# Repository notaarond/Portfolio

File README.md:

# My Small Work Collection !

Some PCB Projects I've done:

- Breakout Board for a TPS3702 Voltage Watchdog Chip
- The "Powerboard":  A Power Hub PCB with 3 Voltage Regulators and Headers for Each
- Sprinkle: ESP-32 based Avionics Board for a 2-Stage Rocket (currently still in progress)
  - not my original design, but was handed over to me minimize and add new sensors, test points, storage systems, and to do some general cleaning up of schematics and silkscreen!

Projects done in Altium or Kicad 7 :)

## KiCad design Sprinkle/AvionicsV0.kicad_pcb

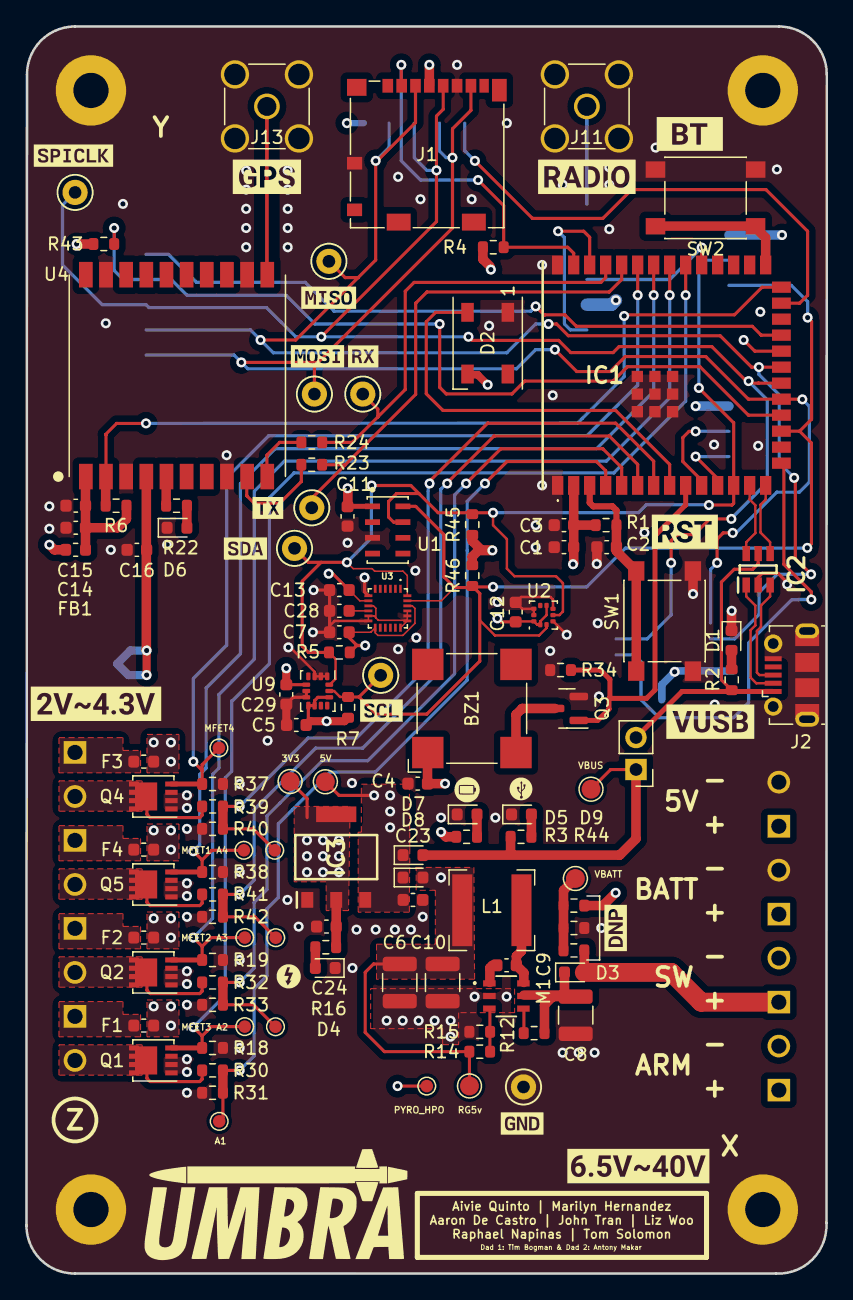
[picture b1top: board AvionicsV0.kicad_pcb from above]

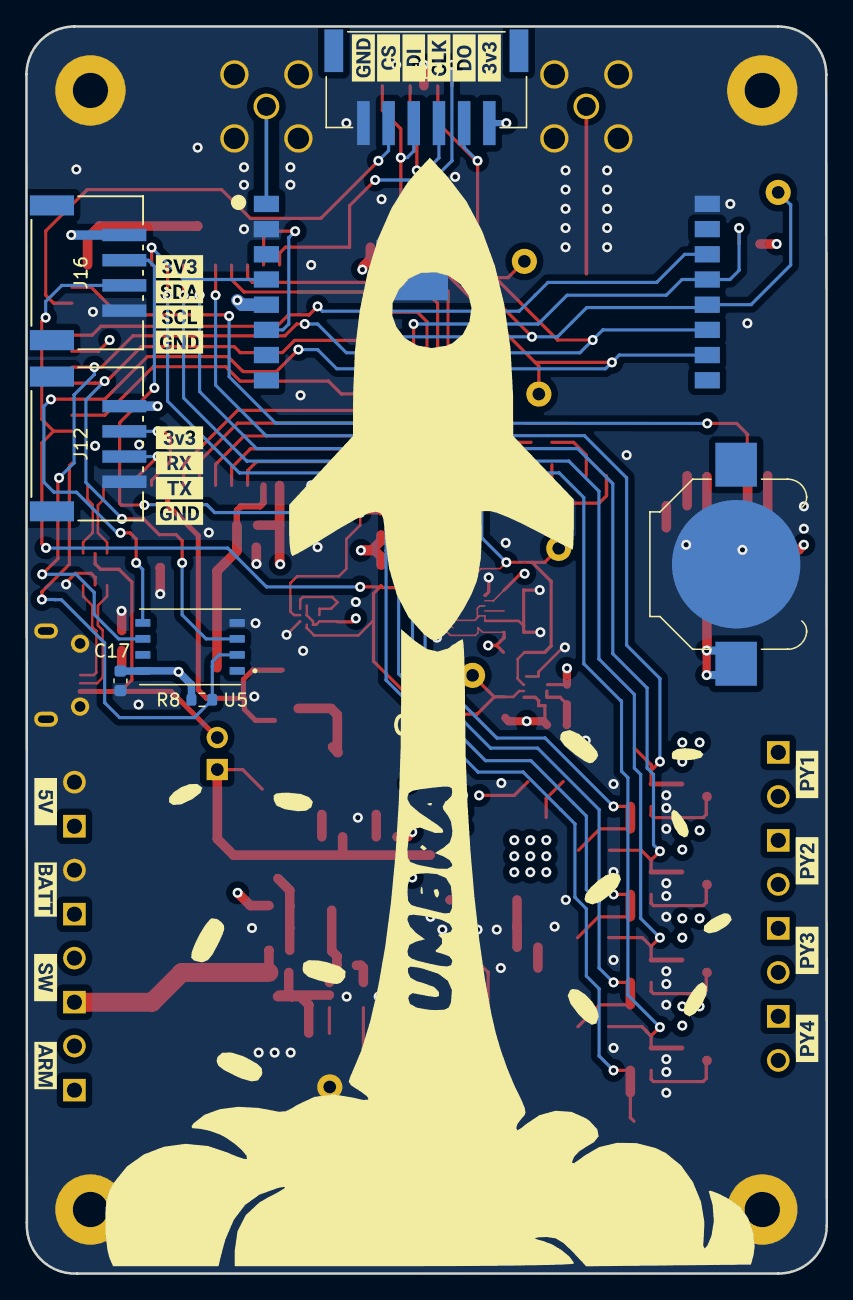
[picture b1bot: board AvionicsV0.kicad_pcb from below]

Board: 4 copper layers, 63.5 x 99.0 mm, 171 parts (30 on the bottom side), 68 nets.

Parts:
BT1: 3.7V LION; BatteryHolder_Keystone_3000_1x12mm
BZ1: Buzzer; MagneticBuzzer_CUI_CMT-8504-100-SMT
C1: 22uF; C_0603_1608Metric
C2, C14, C16: 1uF; C_0603_1608Metric
C3, C12: 100nF; C_0603_1608Metric
C4, C23, C24: 10uF; C_0603_1608Metric
C5, C29: 100 nF; C_0603_1608Metric
C6, C10: 22u; C_1210_3225Metric
C7, C13, C28: 0.1 uF; C_0603_1608Metric
C8: 47u; C_1210_3225Metric
C9: 100n; C_0603_1608Metric
C11: 220nF; C_0603_1608Metric
C15: 0.01uF; C_0603_1608Metric
C17: 0.1uF; C_0603_1608Metric
D1, D4, D5, D6, D9: LED; LED_0603_1608Metric
D2: NeoPixel_THT; LED_WS2812B_PLCC4_5.0x5.0mm_P3.2mm
D3, D7, D8: D_Schottky; D_0603_1608Metric
F1, F2, F3, F4: Fuse; Fuse_0603_1608Metric
FB1: FerriteBead; L_0603_1608Metric
H1, H2, H3, H4: MountingHole_Pad; MountingHole_3.5mm_Pad
IC1: ESP32-S3-WROOM-1U-N4R2; ESP32S3WROOM1UN4R2
IC2: USBLC6-2SC6; SOT95P280X145-6N
IC3: NCP1117IST33T3G; SOT230P700X180-4N
J1: Micro_SD_Card; microSD_HC_Molex_104031-0811
J2: USB_B_Micro; USB_Micro-B_Molex-105017-0001
J3, J4, J6, J7, J8, J9, J10, J14: Conn_01x02; OST_OSTTE020104
J5: Conn_01x02; PinHeader_1x02_P2.54mm_Vertical
J11, J13: Conn_Coaxial; SMA_Amphenol_901-144_Vertical
J12, J16: Conn_01x04; CONN_S4B-PH-SM4-TBLFSN_JST
J17: Conn_01x06; JST_S6B-PH-SM4-TB(LF)(SN)
L1: 22u; L_Bourns-SRN6028
M1: TP6841S6-A; SOT32-6 TP6841S6-TP6841S6-A
Q1, Q2, Q4, Q5: SIR182DP-T1-RE3; Vishay_PowerPAK_1212-8_Single
Q3: 2N7002H; SOT-23
R1, R4, R6, R8, R34, R43: 10k; R_0603_1608Metric
R2, R3, R44: 100; R_0603_1608Metric
R5, R7, R45, R46: 4.7k; R_0603_1608Metric
R10, R30, R32, R39, R41: 350k; R_0603_1608Metric
R11, R12, R31, R33, R40, R42: 100k; R_0603_1608Metric
R13: 0; R_0603_1608Metric
R14: 126k; R_0603_1608Metric
R15: 24k; R_0603_1608Metric
R16: 65; R_0603_1608Metric
R18, R19, R37, R38: 1k; R_0603_1608Metric
R22, R23, R24: 470; R_0603_1608Metric
SW1, SW2: SW_Push; SW_Push_1P1T_NO_6x6mm_H9.5mm
TP1: Vbatt TP; TestPoint_Pad_D1.5mm
TP2: GND TP; TestPoint_Keystone_5000-5004_Miniature
TP3: 3V3 TP; TestPoint_Pad_D1.5mm
TP4: 5V TP; TestPoint_Pad_D1.5mm
TP5: Vbus TP; TestPoint_Pad_D1.5mm
TP6: RG5 TP; TestPoint_Pad_D1.5mm
TP7: SCL TP; TestPoint_Keystone_5000-5004_Miniature
TP8: SDA TP; TestPoint_Keystone_5000-5004_Miniature
TP9: GPS-TX-UART TP; TestPoint_Keystone_5000-5004_Miniature
TP10: GPS-RX-UART-TP; TestPoint_Keystone_5000-5004_Miniature
TP13: SPI-MISO; TestPoint_Keystone_5000-5004_Miniature
TP14: SPI-MOSI; TestPoint_Keystone_5000-5004_Miniature
TP15: SPI-CLK; TestPoint_Keystone_5000-5004_Miniature
TP16: Pyro-MFET4-TP; TestPoint_Pad_D1.0mm
TP17: Pyro-MFET1-TP; TestPoint_Pad_D1.0mm
TP18, TP19: Pyro-MFET2-TP; TestPoint_Pad_D1.0mm
TP20: Pyro-HPO-TP; TestPoint_Pad_D1.0mm
TP21: Cont-A4-TP; TestPoint_Pad_D1.0mm
TP22: Cont-A3-TP; TestPoint_Pad_D1.0mm
TP23: Cont-A2-TP; TestPoint_Pad_D1.0mm
TP24: Cont-A1-TP; TestPoint_Pad_D1.0mm
U1: MS8607; MS860702BA01-50
U2: LPS22HB; ST_HLGA-10_2x2mm_P0.5mm_LayoutBorder3x2y
U3: ICM-20649; QFN40P300X300X95-24N
U4: FGPMMOPA6H
U5: XTSD04GLGEAG; SON127P600X800X95-8N
U8: RFM98PW; RFM95PW
U9: LSM6DS3; LGA-14_3x2.5mm_P0.5mm_LayoutBorder3x4y
kibuzzard-63F7FA90: G***; kibuzzard-63F7FA90
kibuzzard-63F7FAE8: G***; kibuzzard-63F7FAE8
kibuzzard-63F7FC73: G***; kibuzzard-63F7FC73
kibuzzard-63F7FCC0: G***; kibuzzard-63F7FCC0
kibuzzard-63F7FE2E: G***; kibuzzard-63F7FE2E
kibuzzard-63F7FEBE: G***; kibuzzard-63F7FEBE
kibuzzard-640BCAC3: G***; kibuzzard-640BCAC3
kibuzzard-640BCB6B: G***; kibuzzard-640BCB6B
kibuzzard-640BCB88: G***; kibuzzard-640BCB88
kibuzzard-640BCBB0: G***; kibuzzard-640BCBB0
kibuzzard-640BCD9E: G***; kibuzzard-640BCD9E
kibuzzard-640BCD14: G***; kibuzzard-640BCD14
kibuzzard-640BCD52: G***; kibuzzard-640BCD52
kibuzzard-640BCD74: G***; kibuzzard-640BCD74
kibuzzard-640E8E65: G***; kibuzzard-640E8E65
kibuzzard-6400ED13: G***; kibuzzard-6400ED13
kibuzzard-6400EEBB: G***; kibuzzard-6400EEBB
kibuzzard-6400EEFF: G***; kibuzzard-6400EEFF
kibuzzard-6400F0D2: G***; kibuzzard-6400F0D2
kibuzzard-6408D1E8: G***; kibuzzard-6408D1E8
kibuzzard-6408D004: G***; kibuzzard-6408D004
kibuzzard-6408D023: G***; kibuzzard-6408D023
kibuzzard-6408D049, kibuzzard-6408D049#2: G***; kibuzzard-6408D049
kibuzzard-6408D189: G***; kibuzzard-6408D189
kibuzzard-6408D243: G***; kibuzzard-6408D243
kibuzzard-6408D283: G***; kibuzzard-6408D283
kibuzzard-6562B80B: G***; kibuzzard-6562B80B
kibuzzard-6562B89C: G***; kibuzzard-6562B89C
kibuzzard-6562B97E: G***; kibuzzard-6562B97E
kibuzzard-6562B902: G***; kibuzzard-6562B902
kibuzzard-6562B960: G***; kibuzzard-6562B960
kibuzzard-6562B984: G***; kibuzzard-6562B984
kibuzzard-6562F5B5: G***; kibuzzard-6562F5B5
kibuzzard-6562F408: G***; kibuzzard-6562F408
kibuzzard-64010B11, kibuzzard-64010B11#2: G***; kibuzzard-64010B11
kibuzzard-64010B95: G***; kibuzzard-64010B95

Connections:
+3V3: C1.1, C3.1, C5.1, C7.1, C11.1, C12.1, C13.1, C17.1, C24.1, C29.1, FB1.1, IC1.2 (3V3), IC3.2 (V0), IC3.4 (VI), J1.4 (VDD), J12.1, J16.1, J17.1, R1.1, R4.1, R5.1, R7.1, R8.1, R16.1, R43.1, R45.1, R46.1, TP3.1, U1.1 (VDD), U2.1 (Vdd_IO), U2.6 (~CS), U2.10 (VDD), U3.8 (VDDIO), U3.13 (VDD), U3.22 (NCS), U5.8 (VDD), U9.5 (VDDIO), U9.8 (VDD), U9.9 (INT2), U9.12 (CS)
+5V: BZ1.1 (-), C4.1, C23.1, D2.3 (VDD), D7.1 (K), D8.1 (K), IC3.3 (VI), J3.1, TP4.1, U8.5 (VCC)
+BATT: J4.2, J6.1, J14.2
A1: IC1.4 (IO4), R30.1, R31.1, TP24.1
A2: IC1.5 (IO5), R32.1, R33.1, TP23.1
A3: IC1.6 (IO6), R41.1, R42.1, TP22.1
A4: IC1.7 (IO7), R39.1, R40.1, TP21.1
AIO1/SD_CS: IC1.39 (IO1), J1.2 (DAT3/CD), R4.2
AIO2/RF1_IO0: IC1.38 (IO2), U8.6 (GPIO_0)
AIO3/XTSD_CS: IC1.15 (IO3), R8.2, U5.2 (SD3/~CS)
AIO10/RF1_CS: IC1.18 (IO10), R43.2, U8.13 (NSS)
AIO17/TX1: IC1.11 (IO18), J12.3
AIO18/RX1: IC1.10 (IO17), J12.2
BOOT: IC1.27 (IO0), SW2.1
BUZZ: IC1.9 (IO16), Q3.1 (G), R34.2
EN: C2.2, IC1.3 (EN), R1.2, SW1.2
GND: BT1.2 (-), C1.2, C2.1, C3.2, C4.2, C5.2, C6.2, C7.2, C8.2, C10.1, C11.2, C12.2, C13.2, C14.2, C15.2, C16.2, C17.2, C23.2, C24.2, C28.2, C29.2, D1.1 (K), D2.1 (DOUT), D4.1 (K), D5.1 (K), D6.1 (K), D9.1 (K), H1.1, H2.1, H3.1, H4.1, IC1.1 (GND_1), IC1.40 (GND_2), IC1.41 (GND_3), IC1.42 (GND_4), IC1.43 (GND_5), IC1.44 (GND_6), IC1.45 (GND_7), IC1.46 (GND_8), IC1.47 (GND_9), IC1.48 (GND_10), IC1.49 (GND_11), IC2.2 (GND), IC3.1 (GND), J1.6 (VSS), J1.9 (SHIELD), J2.5 (GND), J2.6 (Shield), J3.2, J6.2, J11.2 (Ext), J12.4, J13.2 (Ext), J16.4, J17.6, M1.GND, Q1.1, Q1.2, Q1.3, Q2.1, Q2.2, Q2.3, Q3.2 (S), Q4.1, Q4.2, Q4.3, Q5.1, Q5.2, Q5.3, R11.2, R15.2, R18.1, R19.1, R31.2, R33.2, R34.1, R37.1, R38.1, R40.2, R42.2, SW1.1, SW2.2, TP2.1, U1.3 (GND), U2.3 (RES), U2.5 (SA0), U2.8 (GND), U2.9 (GND), U3.7 (AUX_CL), U3.9 (AD0/SDO), U3.11 (FSYNC), U3.12 (INT1), U3.18 (GND), U3.19 (INT2), U3.20 (RESV), U3.21 (AUX_DA), U4.3 (GND), U4.8 (GND), U4.12 (GND), U4.19 (GND), U5.4 (VSS), U8.2 (GND), U8.16 (GND), U8.17 (GND), U9.1 (SDO/SA0), U9.2 (SDX), U9.3 (SCX), U9.6 (GND), U9.7 (GND)
IO21/RF1_RST: IC1.23 (IO21), U8.14 (RESET)
IO38/RF1_IO4: IC1.31 (IO38), U8.4 (GPIO_4)
IO45/TDO: IC1.26 (IO45), R6.1, U4.2 (NRESET)
J17_CS2: IC1.25 (IO48), J17.5
MFET1: IC1.34 (IO41), Q5.4, R38.2, TP17.1
MFET2: IC1.33 (IO40), Q2.4, R19.2, TP18.1
MFET3: IC1.32 (IO39), Q1.4, R18.2, TP19.1
MFET4: IC1.35 (IO42), Q4.4, R37.2, TP16.1
NEO1: D2.2 (GND), IC1.8 (IO15)
unnamed: BT1.1 (+), C16.1, U4.4 (VBACKUP)
unnamed: BZ1.2 (+), Q3.3 (D)
unnamed: C8.1, D3.1 (K), M1.VIN, R12.1
unnamed: C9.1, M1.BST
unnamed: C9.2, L1.1, M1.SW
unnamed: D1.2 (A), R2.2
unnamed: D4.2 (A), R16.2
unnamed: D5.2 (A), R3.2
unnamed: D6.2 (A), R22.1
unnamed: D9.2 (A), R44.2
unnamed: F1.2, J7.1
unnamed: J7.2, Q1.5, R30.2
unnamed: F2.2, J8.1
unnamed: J8.2, Q2.5, R32.2
unnamed: F3.2, J9.1
unnamed: J9.2, Q4.5, R39.2
unnamed: F4.2, J10.1
unnamed: J10.2, Q5.5, R41.2
unnamed: J13.1 (In), U4.11 (EX_ANT)
unnamed: M1.EN, R12.2
unnamed: M1.FB, R14.2, R15.1
unnamed: C28.1, U3.10 (REGOUT)
unnamed: R22.2, U4.5 (3D-FIX)
unnamed: R24.2, U4.10 (RX)
unnamed: R23.2, U4.9 (TX)
unnamed: C14.1, C15.1, FB1.2, R6.2, U4.1 (VCC)
PYRO_HPO: F1.1, F2.1, F3.1, F4.1, J14.1, TP20.1
RG5v: C6.1, C10.2, D8.2 (A), L1.2, R3.1, R14.1, TP6.1
RX: IC1.37 (TXD0), R24.1, TP10.1
SCL: IC1.17 (IO9), J16.3, R7.2, R46.2, TP7.1, U1.8 (SCL), U2.2 (SCL), U3.23 (SCL/SCLK), U9.13 (SCL)
SDA: IC1.12 (IO8), J16.2, R5.2, R45.2, TP8.1, U1.7 (SDA), U2.4 (SDA), U3.24 (SDA/SDI), U9.14 (SDA)
SPICLK: IC1.20 (IO12), J1.5 (CLK), J17.3, TP15.1, U5.3 (CLK), U8.12 (SCK)
SPID: IC1.19 (IO11), J1.7 (DAT0), J17.4, TP14.1, U5.5 (CMD/DI), U8.10 (MISO)
SPIQ: IC1.21 (IO13), J1.3 (CMD), J17.2, TP13.1, U5.6 (SD0/DO), U8.11 (MOSI)
TX: IC1.36 (RXD0), R23.1, TP9.1
USB_D+: IC1.14 (IO20), IC2.3 (I/O2_1), IC2.4 (I/O2_2), J2.3 (D+)
USB_D-: IC1.13 (IO19), IC2.1 (I/O1_1), IC2.6 (I/O1_2), J2.2 (D-)
VBATT: IC1.22 (IO14), R13.1
VBUS: D7.2 (A), J5.1, R44.1, TP5.1
VCC: D3.2 (A), J4.1, R10.1
VUSB: IC2.5 (VBUS), J2.1 (VBUS), J5.2, R2.1
Vbatt TP: R10.2, R11.1, R13.2, TP1.1

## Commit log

2023-11-13 Add files via upload
    adding TPS3702 breakout project
2023-11-13 Add files via upload
    adding Powerboard Altium files !
2023-11-13 Add files via upload
    adding Sprinkle files !
